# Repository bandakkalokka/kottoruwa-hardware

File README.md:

<!--
*** Thanks for checking out this README Template. If you have a suggestion that would
*** make this better, please fork the repo and create a pull request or simply open
*** an issue with the tag "enhancement".
*** Thanks again! Now go create something AMAZING! :D
-->

<!-- PROJECT SHIELDS -->
<!--
*** I'm using markdown "reference style" links for readability.
*** Reference links are enclosed in brackets [ ] instead of parentheses ( ).
*** See the bottom of this document for the declaration of the reference variables
*** for contributors-url, forks-url, etc. This is an optional, concise syntax you may use.
*** https://www.markdownguide.org/basic-syntax/#reference-style-links
-->
[![Contributors][contributors-shield]][contributors-url]
[![Forks][forks-shield]][forks-url]
[![Stargazers][stars-shield]][stars-url]
[![Issues][issues-shield]][issues-url]
[![MIT License][license-shield]][license-url]
<!-- [![LinkedIn][linkedin-shield]][linkedin-url] -->

<!-- PROJECT LOGO -->
<br />
<p align="center">

  <h3 align="center">Kottoruwa</h3>

  <p align="center">
    An awesome wireless mechanical keyboard with Li-Ion Battery Managemet, 2.4GHz radio and an OLED Display!
    <br />
    <a href="https://github.com/bandakkalokka/kottoruwa-hardware"><strong>Explore the docs »</strong></a>
    <br />
    <br />
    <!-- <a href="https://github.com/othneildrew/Best-README-Template">View Demo</a> 
    · -->
    <a href="https://github.com/bandakkalokka/kottoruwa-hardware/issues">Report Bug</a>
    ·
    <a href="https://github.com/bandakkalokka/kottoruwa-hardware/issues">Request Feature</a>
  </p>
</p>

<!-- TABLE OF CONTENTS -->
## Table of Contents

* [About the Project](#about-the-project)
  * [Built With](#built-with)
* [Project Structure](#project-structure)
* [Prerequisites](#prerequisites)
* [Roadmap](#roadmap)
* [Contributing](#contributing)
* [License](#license)
* [Contact](#contact)
* [Acknowledgements](#acknowledgements)

[![Product Name Screen Shot][product-screenshot]](https://example.com)

### Built With
* [KiCAD](https://docs.kicad-pcb.org/5.0/en/kicad/kicad.html)
* [QMK](https://qmk.fm/)

<!-- GETTING STARTED -->
## Project Structure

* 3d_models - .STEP and .WRL model files for all footprints
* datasheets - data sheets for components used
* gerbers - final production files
* images - SVG images and 3D board renders
* keeb-design-files - .pro, .sch and other KiCAD files
* lib_fp.pretty - footprints
* lib_sch - schematic symbols
* pdf - schematics, board layouts, dimension drawings

### Prerequisites

* KICAD (EESchema, PcbNew)
* PDF Viewer
* 3D Model Viewer

<!-- ROADMAP -->
## Roadmap

See the [open issues](https://github.com/bandakkalokka/kottoruwa-hardware/issues) for a list of proposed features (and known issues).

<!-- CONTRIBUTING -->
## Contributing

Contributions are what make the open source community such an amazing place to be learn, inspire, and create. Any contributions you make are **greatly appreciated**.

1. Fork the Project
2. Create your Feature Branch (`git checkout -b feature/AmazingFeature`)
3. Commit your Changes (`git commit -m 'Add some AmazingFeature'`)
4. Push to the Branch (`git push origin feature/AmazingFeature`)
5. Open a Pull Request

<!-- LICENSE -->
## License

Distributed under the GPL-3.0 License. See `LICENSE` for more information.

<!-- CONTACT -->
## Contact

rb28z2 - [@rb28z2](https://github.com/rb28z2) 
<br />
bandakkalokka - [@bandakkalokka](https://github.com/bandakkalokka)
<br />
Project Link: [https://github.com/bandakkalokka/kottoruwa-hardware](https://github.com/bandakkalokka/kottoruwa-hardware)

<!-- ACKNOWLEDGEMENTS -->
## 

* [QMK](https://github.com/qmk/qmk_firmware)

<!-- MARKDOWN LINKS & IMAGES -->
<!-- https://www.markdownguide.org/basic-syntax/#reference-style-links -->
[contributors-shield]: https://img.shields.io/github/contributors/bandakkalokka/kottoruwa-hardware.svg?style=flat-square
[contributors-url]: https://github.com/bandakkalokka/kottoruwa-hardware/graphs/contributors
[forks-shield]: https://img.shields.io/github/forks/bandakkalokka/kottoruwa-hardware.svg?style=flat-square
[forks-url]: https://github.com/bandakkalokka/kottoruwa-hardware/network/members
[stars-shield]: https://img.shields.io/github/stars/bandakkalokka/kottoruwa-hardware.svg?style=flat-square
[stars-url]: https://github.com/bandakkalokka/kottoruwa-hardware/stargazers
[issues-shield]: https://img.shields.io/github/issues/bandakkalokka/kottoruwa-hardware.svg?style=flat-square
[issues-url]: https://github.com/bandakkalokka/kottoruwa-hardware/issues
[license-shield]: https://img.shields.io/github/license/bandakkalokka/kottoruwa-hardware.svg?style=flat-square
[license-url]: https://github.com/bandakkalokka/kottoruwa-hardware/blob/master/LICENSE.txt
[linkedin-shield]: https://img.shields.io/badge/-LinkedIn-black.svg?style=flat-square&logo=linkedin&colorB=555
[linkedin-url]: https://linkedin.com/in/chathula-adikary-908450168/
[product-screenshot]: images/keeb-img.jpg

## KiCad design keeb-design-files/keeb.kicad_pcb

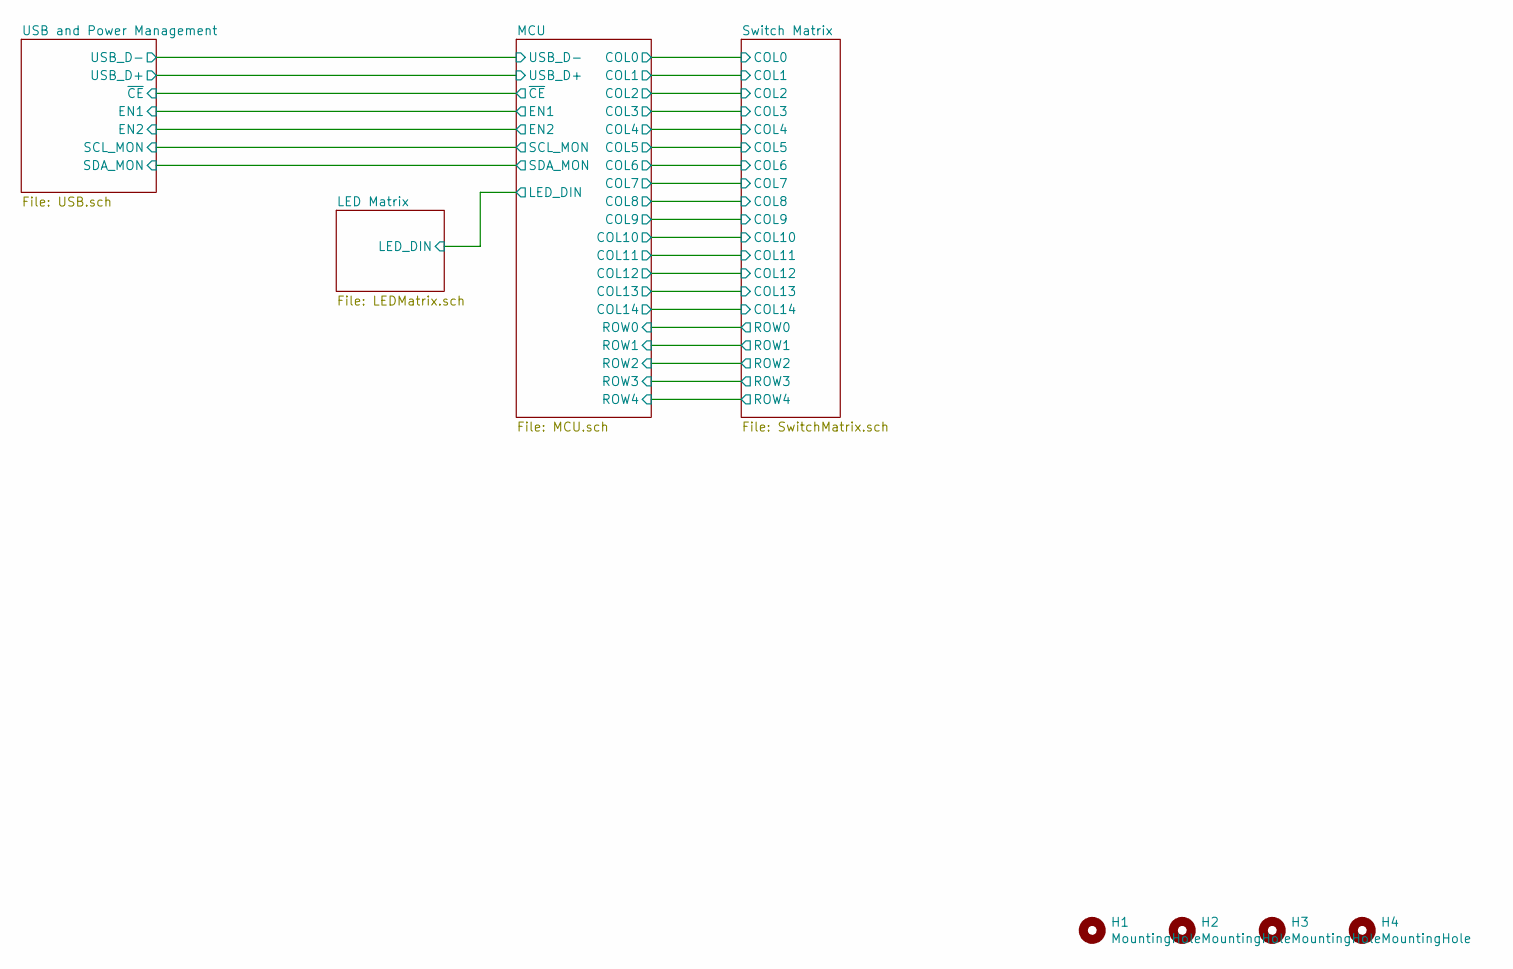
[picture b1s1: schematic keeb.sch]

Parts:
H1, H2, H3, H4: MountingHole; MountingHole_4.3mm_M4

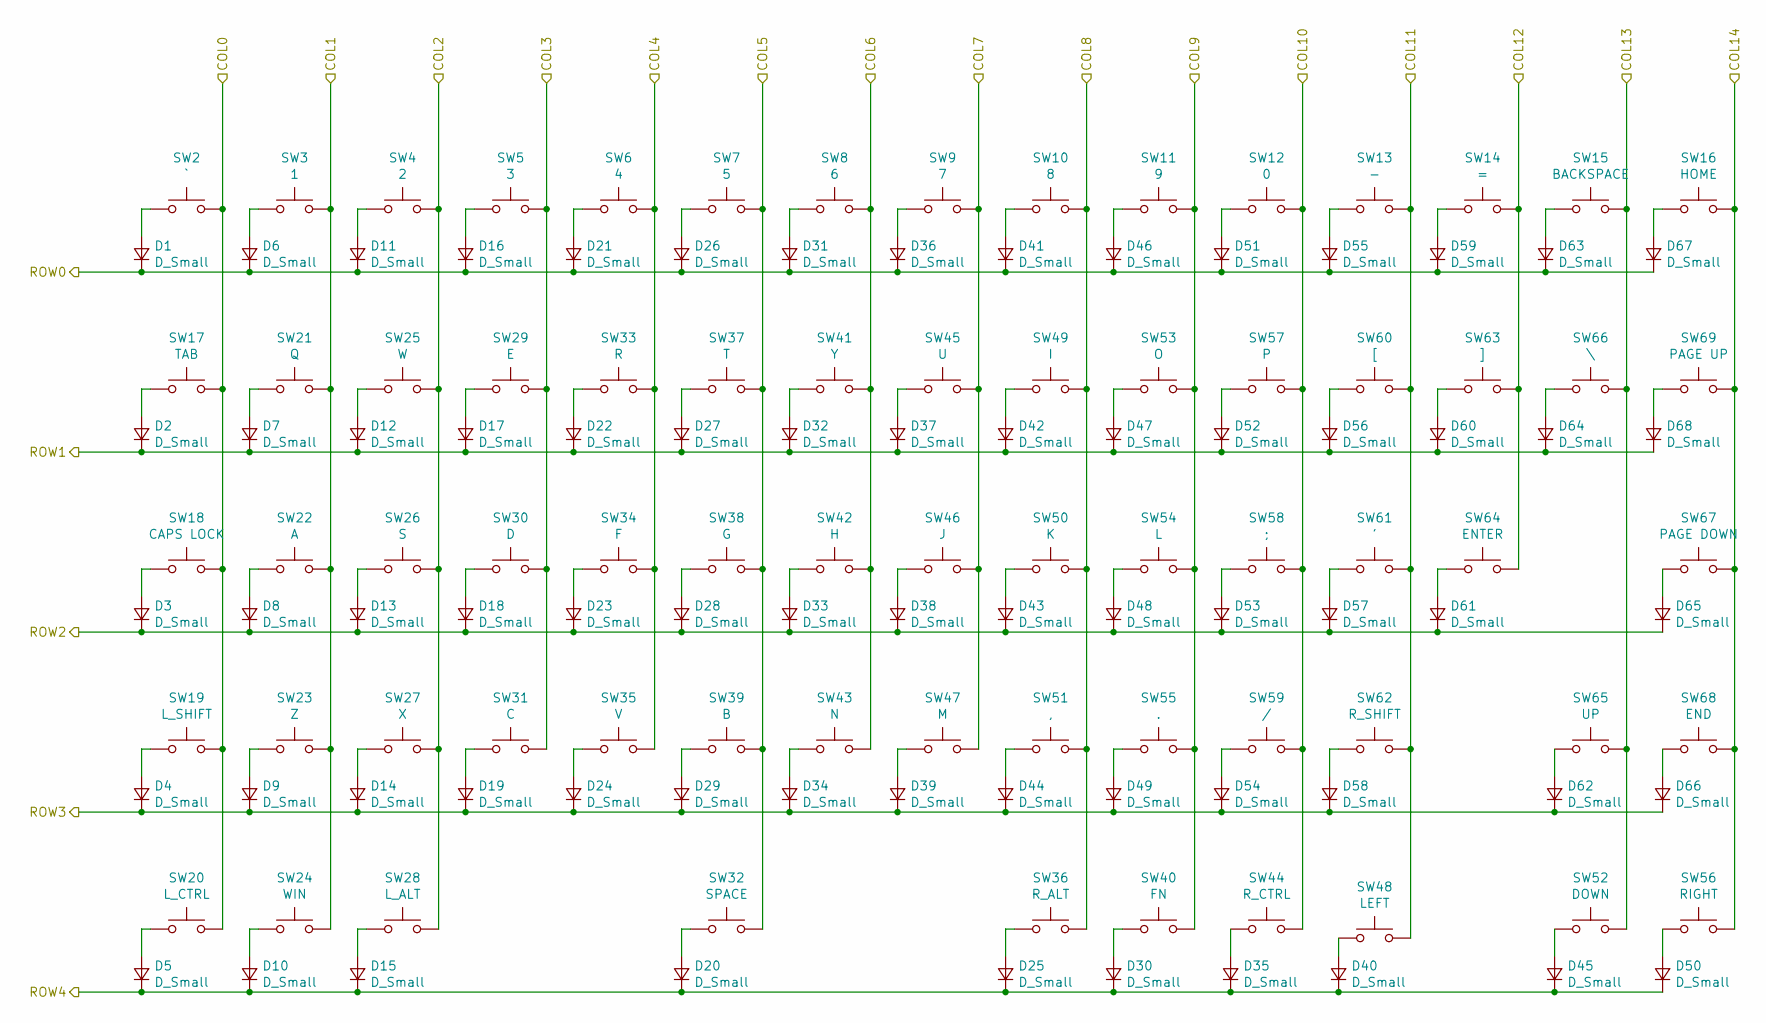
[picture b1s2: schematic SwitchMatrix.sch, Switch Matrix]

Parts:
D1, D2, D3, D4, D5, D6, D7, D8, D9, D10, D11, D12, D13, D14, D15, D16, D17, D18, D19, D20, D21, D22, D23, D24, D25, D26, D27, D28, D29, D30, D31, D32, D33, D34, D35, D36, D37, D38, D39, D40, D41, D42, D43, D44, D45, D46, D47, D48, D49, D50, D51, D52, D53, D54, D55, D56, D57, D58, D59, D60, D61, D62, D63, D64, D65, D66, D67, D68: D_Small; D_SOD-323_HandSoldering; LCSC Part Number C2128
SW2: `; MXOnly-1U-Hotswap
SW3: 1; MXOnly-1U-Hotswap
SW4: 2; MXOnly-1U-Hotswap
SW5: 3; MXOnly-1U-Hotswap
SW6: 4; MXOnly-1U-Hotswap
SW7: 5; MXOnly-1U-Hotswap
SW8: 6; MXOnly-1U-Hotswap
SW9: 7; MXOnly-1U-Hotswap
SW10: 8; MXOnly-1U-Hotswap
SW11: 9; MXOnly-1U-Hotswap
SW12: 0; MXOnly-1U-Hotswap
SW13: -; MXOnly-1U-Hotswap
SW14: =; MXOnly-1U-Hotswap
SW15: BACKSPACE; MXOnly-2U-Hotswap
SW16: HOME; MXOnly-1U-Hotswap
SW17: TAB; MXOnly-1.5U-Hotswap
SW18: CAPS LOCK; MXOnly-1.75U-Hotswap
SW19: L_SHIFT; MXOnly-2.25U-Hotswap
SW20: L_CTRL; MXOnly-1.25U-Hotswap
SW21: Q; MXOnly-1U-Hotswap
SW22: A; MXOnly-1U-Hotswap
SW23: Z; MXOnly-1U-Hotswap
SW24: WIN; MXOnly-1.25U-Hotswap
SW25: W; MXOnly-1U-Hotswap
SW26: S; MXOnly-1U-Hotswap
SW27: X; MXOnly-1U-Hotswap
SW28: L_ALT; MXOnly-1.25U-Hotswap
SW29: E; MXOnly-1U-Hotswap
SW30: D; MXOnly-1U-Hotswap
SW31: C; MXOnly-1U-Hotswap
SW32: SPACE; MXOnly-6.25U-Hotswap
SW33: R; MXOnly-1U-Hotswap
SW34: F; MXOnly-1U-Hotswap
SW35: V; MXOnly-1U-Hotswap
SW36: R_ALT; MXOnly-1U-Hotswap
SW37: T; MXOnly-1U-Hotswap
SW38: G; MXOnly-1U-Hotswap
SW39: B; MXOnly-1U-Hotswap
SW40: FN; MXOnly-1U-Hotswap
SW41: Y; MXOnly-1U-Hotswap
SW42: H; MXOnly-1U-Hotswap
SW43: N; MXOnly-1U-Hotswap
SW44: R_CTRL; MXOnly-1U-Hotswap
SW45: U; MXOnly-1U-Hotswap
SW46: J; MXOnly-1U-Hotswap
SW47: M; MXOnly-1U-Hotswap
SW48: LEFT; MXOnly-1U-Hotswap
SW49: I; MXOnly-1U-Hotswap
SW50: K; MXOnly-1U-Hotswap
SW51: ,; MXOnly-1U-Hotswap
SW52: DOWN; MXOnly-1U-Hotswap
SW53: O; MXOnly-1U-Hotswap
SW54: L; MXOnly-1U-Hotswap
SW55: .; MXOnly-1U-Hotswap
SW56: RIGHT; MXOnly-1U-Hotswap
SW57: P; MXOnly-1U-Hotswap
SW58: ;; MXOnly-1U-Hotswap
SW59: /; MXOnly-1U-Hotswap
SW60: [; MXOnly-1U-Hotswap
SW61: '; MXOnly-1U-Hotswap
SW62: R_SHIFT; MXOnly-1.75U-Hotswap
SW63: ]; MXOnly-1U-Hotswap
SW64: ENTER; MXOnly-2.25U-Hotswap
SW65: UP; MXOnly-1U-Hotswap
SW66: \\; MXOnly-1.5U-Hotswap
SW67: PAGE DOWN; MXOnly-1U-Hotswap
SW68: END; MXOnly-1U-Hotswap
SW69: PAGE UP; MXOnly-1U-Hotswap

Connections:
/MCU/COL0: SW2.2, SW17.2, SW18.2, SW19.2, SW20.2; also elsewhere on the board
/MCU/COL1: SW3.2, SW21.2, SW22.2, SW23.2, SW24.2; also elsewhere on the board
/MCU/COL2: SW4.2, SW25.2, SW26.2, SW27.2, SW28.2; also elsewhere on the board
/MCU/COL3: SW5.2, SW29.2, SW30.2, SW31.2; also elsewhere on the board
/MCU/COL4: SW6.2, SW33.2, SW34.2, SW35.2; also elsewhere on the board
/MCU/COL5: SW7.2, SW32.2, SW37.2, SW38.2, SW39.2; also elsewhere on the board
/MCU/COL6: SW8.2, SW41.2, SW42.2, SW43.2; also elsewhere on the board
/MCU/COL7: SW9.2, SW45.2, SW46.2, SW47.2; also elsewhere on the board
/MCU/COL8: SW10.2, SW36.2, SW49.2, SW50.2, SW51.2; also elsewhere on the board
/MCU/COL9: SW11.2, SW40.2, SW53.2, SW54.2, SW55.2; also elsewhere on the board
/MCU/COL10: SW12.2, SW44.2, SW57.2, SW58.2, SW59.2; also elsewhere on the board
/MCU/COL11: SW13.2, SW48.2, SW60.2, SW61.2, SW62.2; also elsewhere on the board
/MCU/COL12: SW14.2, SW63.2, SW64.2; also elsewhere on the board
/MCU/COL13: SW15.2, SW52.2, SW65.2, SW66.2; also elsewhere on the board
/MCU/COL14: SW16.2, SW56.2, SW67.2, SW68.2, SW69.2; also elsewhere on the board
/MCU/ROW0: D1.1 (K), D6.1 (K), D11.1 (K), D16.1 (K), D21.1 (K), D26.1 (K), D31.1 (K), D36.1 (K), D41.1 (K), D46.1 (K), D51.1 (K), D55.1 (K), D59.1 (K), D63.1 (K), D67.1 (K); also elsewhere on the board
/MCU/ROW1: D2.1 (K), D7.1 (K), D12.1 (K), D17.1 (K), D22.1 (K), D27.1 (K), D32.1 (K), D37.1 (K), D42.1 (K), D47.1 (K), D52.1 (K), D56.1 (K), D60.1 (K), D64.1 (K), D68.1 (K); also elsewhere on the board
/MCU/ROW2: D3.1 (K), D8.1 (K), D13.1 (K), D18.1 (K), D23.1 (K), D28.1 (K), D33.1 (K), D38.1 (K), D43.1 (K), D48.1 (K), D53.1 (K), D57.1 (K), D61.1 (K), D65.1 (K); also elsewhere on the board
/MCU/ROW3: D4.1 (K), D9.1 (K), D14.1 (K), D19.1 (K), D24.1 (K), D29.1 (K), D34.1 (K), D39.1 (K), D44.1 (K), D49.1 (K), D54.1 (K), D58.1 (K), D62.1 (K), D66.1 (K); also elsewhere on the board
/MCU/ROW4: D5.1 (K), D10.1 (K), D15.1 (K), D20.1 (K), D25.1 (K), D30.1 (K), D35.1 (K), D40.1 (K), D45.1 (K), D50.1 (K); also elsewhere on the board
unnamed: D1.2 (A), SW2.1
unnamed: D2.2 (A), SW17.1
unnamed: D3.2 (A), SW18.1
unnamed: D4.2 (A), SW19.1
unnamed: D5.2 (A), SW20.1
unnamed: D6.2 (A), SW3.1
unnamed: D7.2 (A), SW21.1
unnamed: D8.2 (A), SW22.1
unnamed: D9.2 (A), SW23.1
unnamed: D10.2 (A), SW24.1
unnamed: D11.2 (A), SW4.1
unnamed: D12.2 (A), SW25.1
unnamed: D13.2 (A), SW26.1
unnamed: D14.2 (A), SW27.1
unnamed: D15.2 (A), SW28.1
unnamed: D16.2 (A), SW5.1
unnamed: D17.2 (A), SW29.1
unnamed: D18.2 (A), SW30.1
unnamed: D19.2 (A), SW31.1
unnamed: D20.2 (A), SW32.1
unnamed: D21.2 (A), SW6.1
unnamed: D22.2 (A), SW33.1
unnamed: D23.2 (A), SW34.1
unnamed: D24.2 (A), SW35.1
unnamed: D25.2 (A), SW36.1
unnamed: D26.2 (A), SW7.1
unnamed: D27.2 (A), SW37.1
unnamed: D28.2 (A), SW38.1
unnamed: D29.2 (A), SW39.1
unnamed: D30.2 (A), SW40.1
unnamed: D31.2 (A), SW8.1
unnamed: D32.2 (A), SW41.1
unnamed: D33.2 (A), SW42.1
unnamed: D34.2 (A), SW43.1
unnamed: D35.2 (A), SW44.1
unnamed: D36.2 (A), SW9.1
unnamed: D37.2 (A), SW45.1
unnamed: D38.2 (A), SW46.1
unnamed: D39.2 (A), SW47.1
unnamed: D40.2 (A), SW48.1
unnamed: D41.2 (A), SW10.1
unnamed: D42.2 (A), SW49.1
unnamed: D43.2 (A), SW50.1
unnamed: D44.2 (A), SW51.1
unnamed: D45.2 (A), SW52.1
unnamed: D46.2 (A), SW11.1
unnamed: D47.2 (A), SW53.1
unnamed: D48.2 (A), SW54.1
unnamed: D49.2 (A), SW55.1
unnamed: D50.2 (A), SW56.1
unnamed: D51.2 (A), SW12.1
unnamed: D52.2 (A), SW57.1
unnamed: D53.2 (A), SW58.1
unnamed: D54.2 (A), SW59.1
unnamed: D55.2 (A), SW13.1
unnamed: D56.2 (A), SW60.1
unnamed: D57.2 (A), SW61.1
unnamed: D58.2 (A), SW62.1
unnamed: D59.2 (A), SW14.1
unnamed: D60.2 (A), SW63.1
unnamed: D61.2 (A), SW64.1
unnamed: D62.2 (A), SW65.1
unnamed: D63.2 (A), SW15.1
unnamed: D64.2 (A), SW66.1
unnamed: D65.2 (A), SW67.1
unnamed: D66.2 (A), SW68.1
unnamed: D67.2 (A), SW16.1
unnamed: D68.2 (A), SW69.1

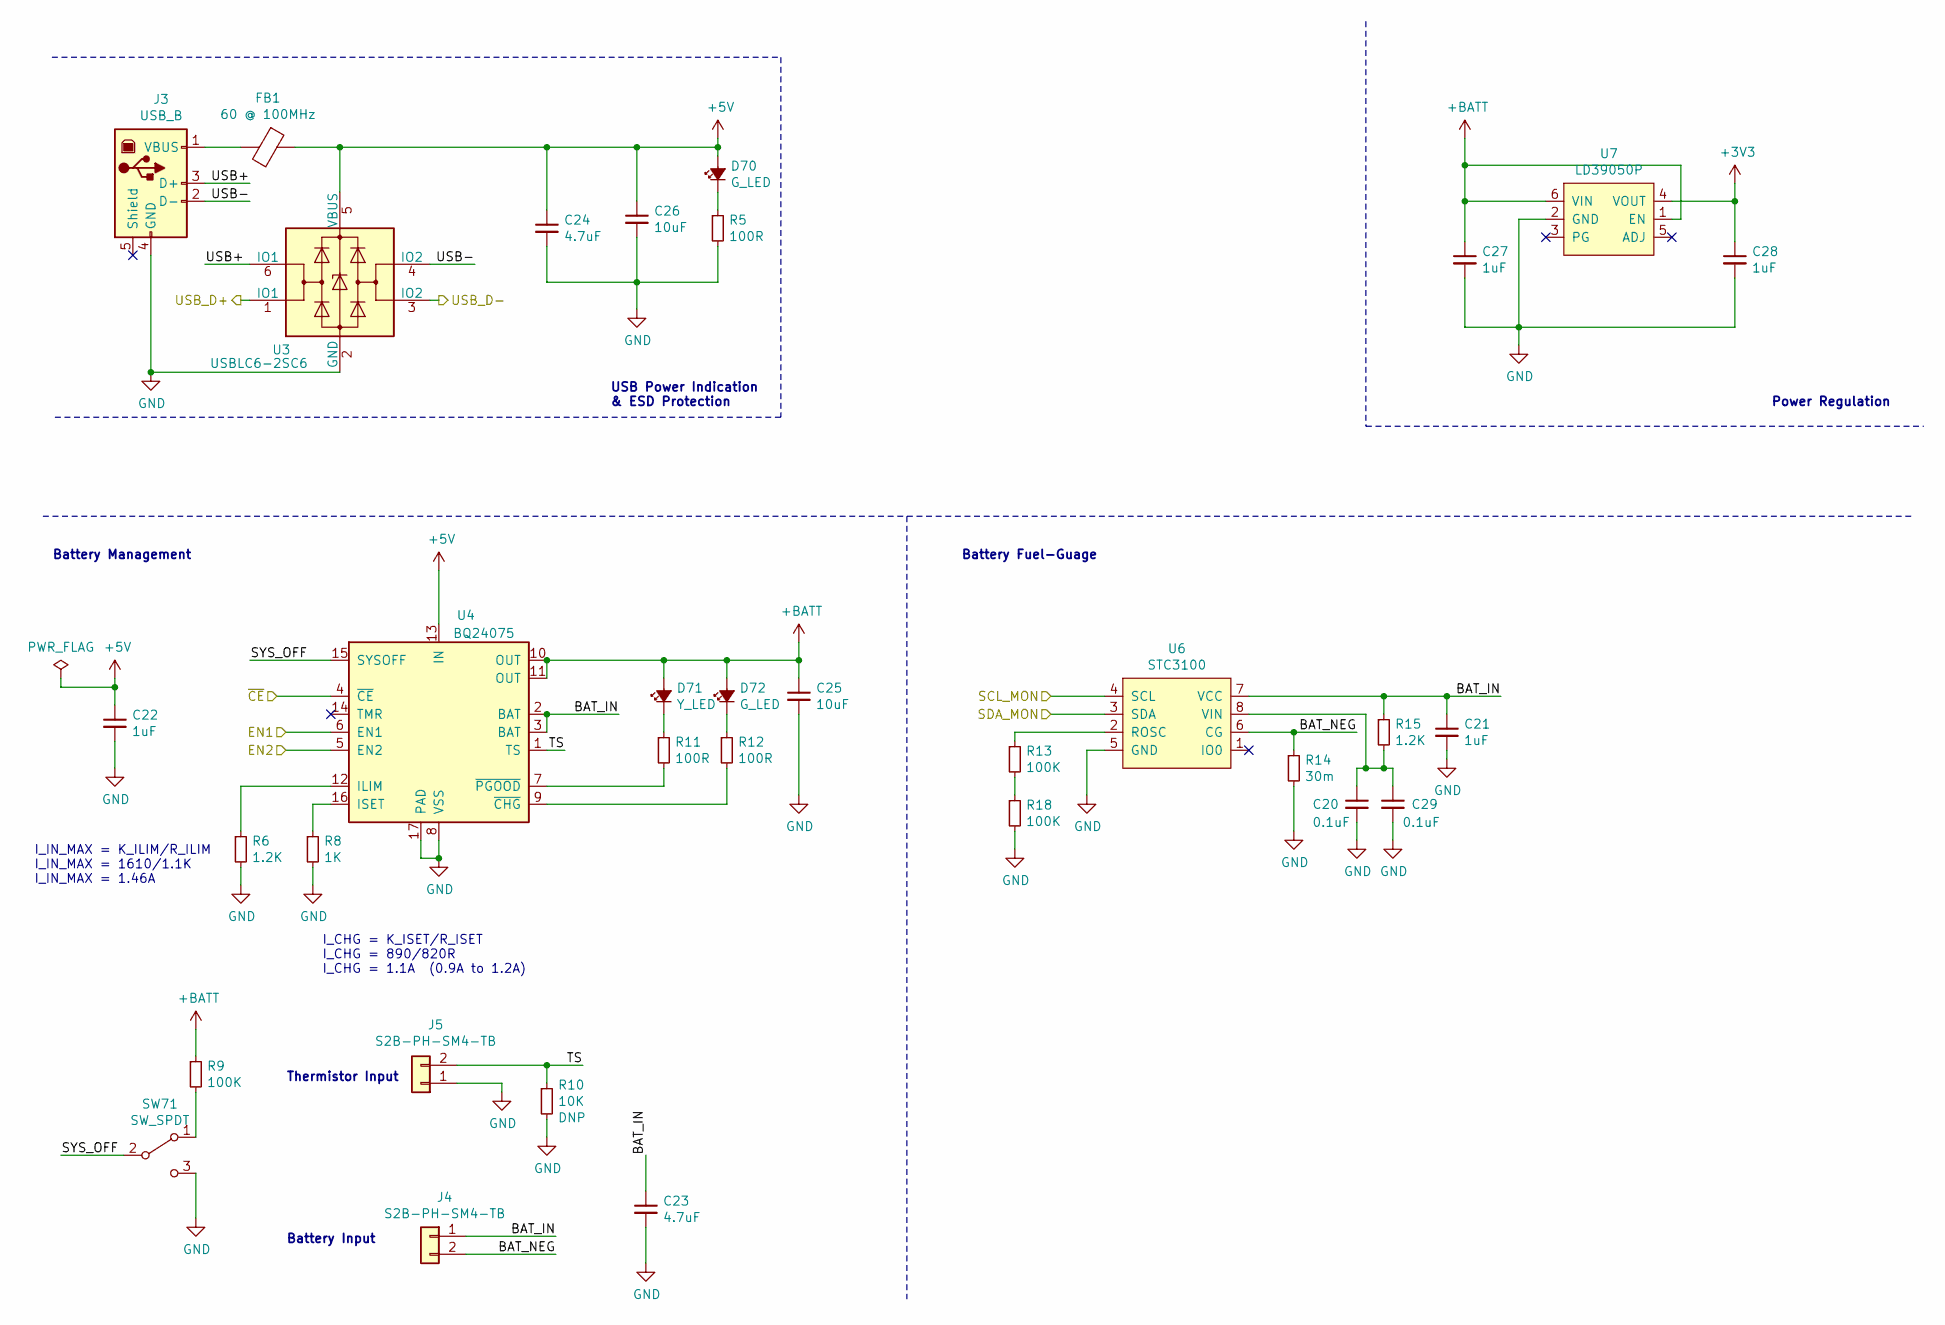
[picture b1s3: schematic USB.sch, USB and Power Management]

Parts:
C20, C29: 0.1uF; C_0402_1005Metric; LCSC Part Number C1525
C21, C22, C27, C28: 1uF; C_0402_1005Metric; LCSC Part Number C52923
C23, C24: 4.7uF; C_0603_1608Metric; LCSC Part Number C19666
C25, C26: 10uF; C_0603_1608Metric; LCSC Part Number C19702
D70, D72: G_LED; LED_0603_1608Metric; LCSC Part Number C72043
D71: Y_LED; LED_0603_1608Metric; LCSC Part Number C72038
FB1: 60 @ 100MHz; R_0603_1608Metric_Pad1.05x0.95mm_HandSolder; LCSC Part Number C76816
J3: USB_B; USB-B1HSW6
J4, J5: S2B-PH-SM4-TB; JST_PH_S2B-PH-SM4-TB_1x02-1MP_P2.00mm_Horizontal
R5, R11, R12: 100R; R_0402_1005Metric; LCSC Part Number C25076
R6, R15: 1.2K; R_0402_1005Metric; LCSC Part Number C25862
R8: 1K; R_0402_1005Metric; LCSC Part Number C11702
R9, R13, R18: 100K; R_0402_1005Metric; LCSC Part Number C25741
R10: 10K; R_0603_1608Metric_Pad1.05x0.95mm_HandSolder; LCSC Part Number DNP
R14: 30m; R_0805_2012Metric; LCSC Part Number C247605
SW71: SW_SPDT; SW_CuK_OS102011MA1QN1_SPDT_Angled
U3: USBLC6-2SC6; SOT-23-6; LCSC Part Number C7519
U4: BQ24075; QFN-16-1EP_3x3mm_P0.5mm_EP1.7x1.7mm; LCSC Part Number C15464
U6: STC3100; DFN-8-1EP_3x3mm_P0.5mm_EP1.66x2.38mm; LCSC Part Number C155587
U7: LD39050P; DFN-6-1EP_3x3mm_P0.95mm_EP1.7x2.6mm; LCSC Part Number C132827

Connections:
+3V3: C28.1, U7.4 (VOUT); also elsewhere on the board
+5V: C22.1, C24.1, C26.1, D70.2 (A), FB1.1, U3.5 (VBUS), U4.13 (IN)
+BATT: C25.1, C27.1, D71.2 (A), D72.2 (A), R9.1, U4.10 (OUT), U4.11 (OUT), U7.1 (EN), U7.6 (VIN)
/MCU/EN1: U4.6 (EN1); also elsewhere on the board
/MCU/EN2: U4.5 (EN2); also elsewhere on the board
/MCU/SCL_MON: U6.4 (SCL); also elsewhere on the board
/MCU/SDA_MON: U6.3 (SDA); also elsewhere on the board
/MCU/USB_D+: U3.1 (IO1); also elsewhere on the board
/MCU/USB_D-: U3.3 (IO2); also elsewhere on the board
/MCU/~CE~: U4.4 (~CE); also elsewhere on the board
/USB and Power Management/BAT_IN: C21.1, C23.1, J4.1, R15.1, U4.2 (BAT), U4.3 (BAT), U6.7 (VCC)
/USB and Power Management/BAT_NEG: J4.2, R14.1, U6.6 (CG)
/USB and Power Management/SYS_OFF: SW71.2 (B), U4.15 (SYSOFF)
/USB and Power Management/TS: J5.2, R10.1, U4.1 (TS)
/USB and Power Management/USB+: J3.3 (D+), U3.6 (IO1)
/USB and Power Management/USB-: J3.2 (D-), U3.4 (IO2)
GND: C20.2, C21.2, C22.2, C23.2, C24.2, C25.2, C26.2, C27.2, C28.2, C29.2, J3.4 (GND), J5.1, R5.2, R6.2, R8.2, R10.2, R14.2, R18.2, SW71.3 (C), U3.2 (GND), U4.8 (VSS), U4.17 (PAD), U6.5 (GND), U6.9, U7.2 (GND), U7.7; also elsewhere on the board
unnamed: C20.1, C29.1, R15.2, U6.8 (VIN)
unnamed: D70.1 (K), R5.1
unnamed: D71.1 (K), R11.1
unnamed: D72.1 (K), R12.1
unnamed: FB1.2, J3.1 (VBUS)
unnamed: R6.1, U4.12 (ILIM)
unnamed: R8.1, U4.16 (ISET)
unnamed: R9.2, SW71.1 (A)
unnamed: R11.2, U4.7 (~PGOOD)
unnamed: R12.2, U4.9 (~CHG)
unnamed: R13.1, U6.2 (ROSC)
unnamed: R13.2, R18.1

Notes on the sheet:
USB Power Indication & ESD Protection
I_CHG = K_ISET/R_ISET I_CHG = 890/820R I_CHG = 1.1A (0.9A to 1.2A)
I_IN_MAX = K_ILIM/R_ILIM I_IN_MAX = 1610/1.1K I_IN_MAX = 1.46A
Power Regulation
Thermistor Input
Battery Input
Battery Management
Battery Fuel-Guage

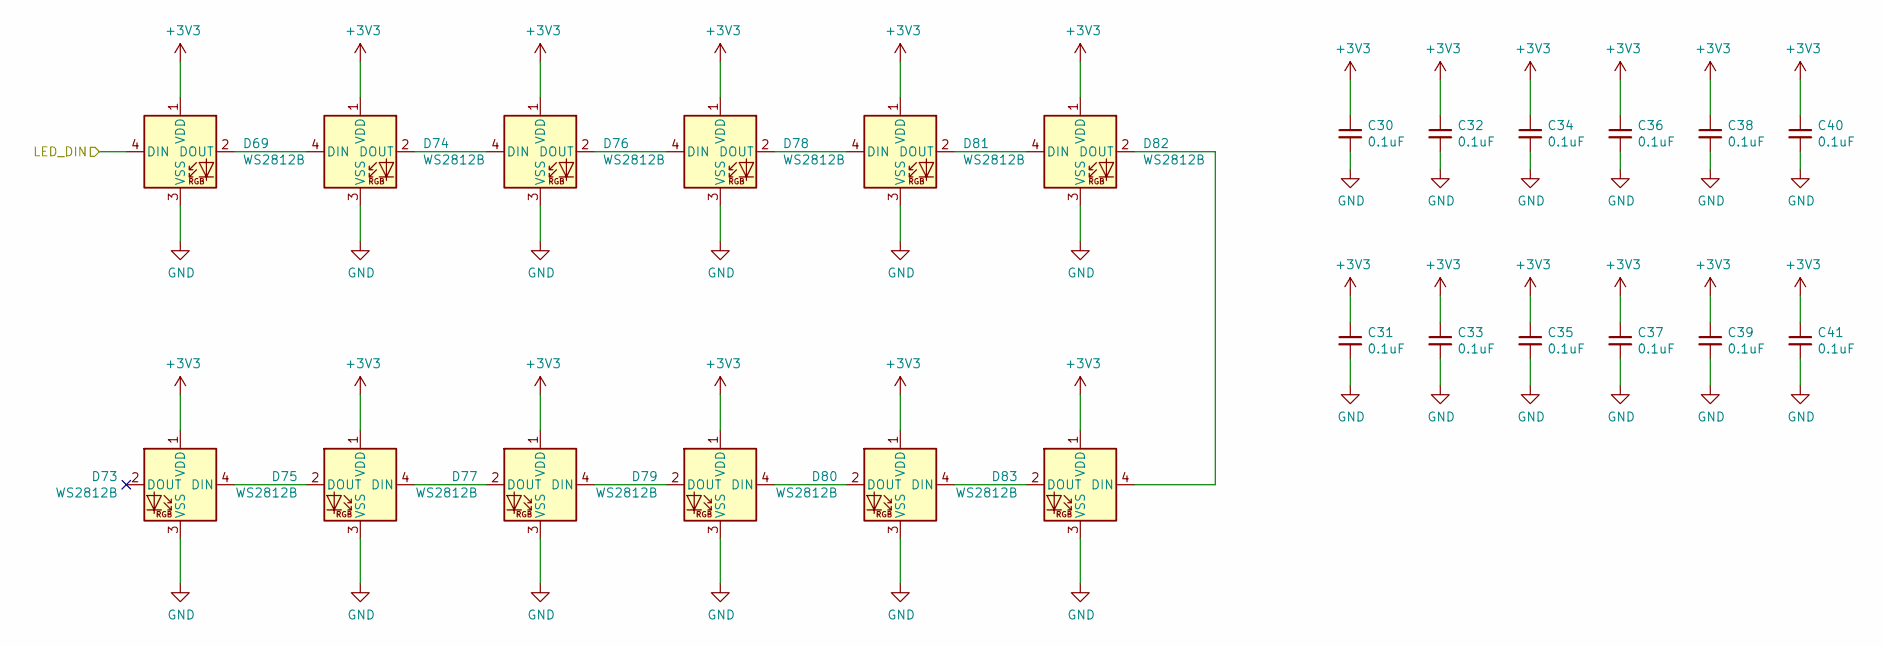
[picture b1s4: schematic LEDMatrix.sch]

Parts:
C30, C31, C32, C33, C34, C35, C36, C37, C38, C39, C40, C41: 0.1uF; C_0402_1005Metric; LCSC Part Number C1525
D69, D73, D74, D75, D76, D77, D78, D79, D80, D81, D82, D83: WS2812B; LED_WS2812B_PLCC4_5.0x5.0mm_P3.2mm; LCSC Part Number C114586

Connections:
+3V3: C30.1, C31.1, C32.1, C33.1, C34.1, C35.1, C36.1, C37.1, C38.1, C39.1, C40.1, C41.1, D69.1 (VDD), D73.1 (VDD), D74.1 (VDD), D75.1 (VDD), D76.1 (VDD), D77.1 (VDD), D78.1 (VDD), D79.1 (VDD), D80.1 (VDD), D81.1 (VDD), D82.1 (VDD), D83.1 (VDD); also elsewhere on the board
/LED Matrix/LED_DIN: D69.4 (DIN); also elsewhere on the board
GND: C30.2, C31.2, C32.2, C33.2, C34.2, C35.2, C36.2, C37.2, C38.2, C39.2, C40.2, C41.2, D69.3 (VSS), D73.3 (VSS), D74.3 (VSS), D75.3 (VSS), D76.3 (VSS), D77.3 (VSS), D78.3 (VSS), D79.3 (VSS), D80.3 (VSS), D81.3 (VSS), D82.3 (VSS), D83.3 (VSS); also elsewhere on the board
unnamed: D69.2 (DOUT), D74.4 (DIN)
unnamed: D73.4 (DIN), D75.2 (DOUT)
unnamed: D74.2 (DOUT), D76.4 (DIN)
unnamed: D75.4 (DIN), D77.2 (DOUT)
unnamed: D76.2 (DOUT), D78.4 (DIN)
unnamed: D77.4 (DIN), D79.2 (DOUT)
unnamed: D78.2 (DOUT), D81.4 (DIN)
unnamed: D79.4 (DIN), D80.2 (DOUT)
unnamed: D80.4 (DIN), D83.2 (DOUT)
unnamed: D81.2 (DOUT), D82.4 (DIN)
unnamed: D82.2 (DOUT), D83.4 (DIN)

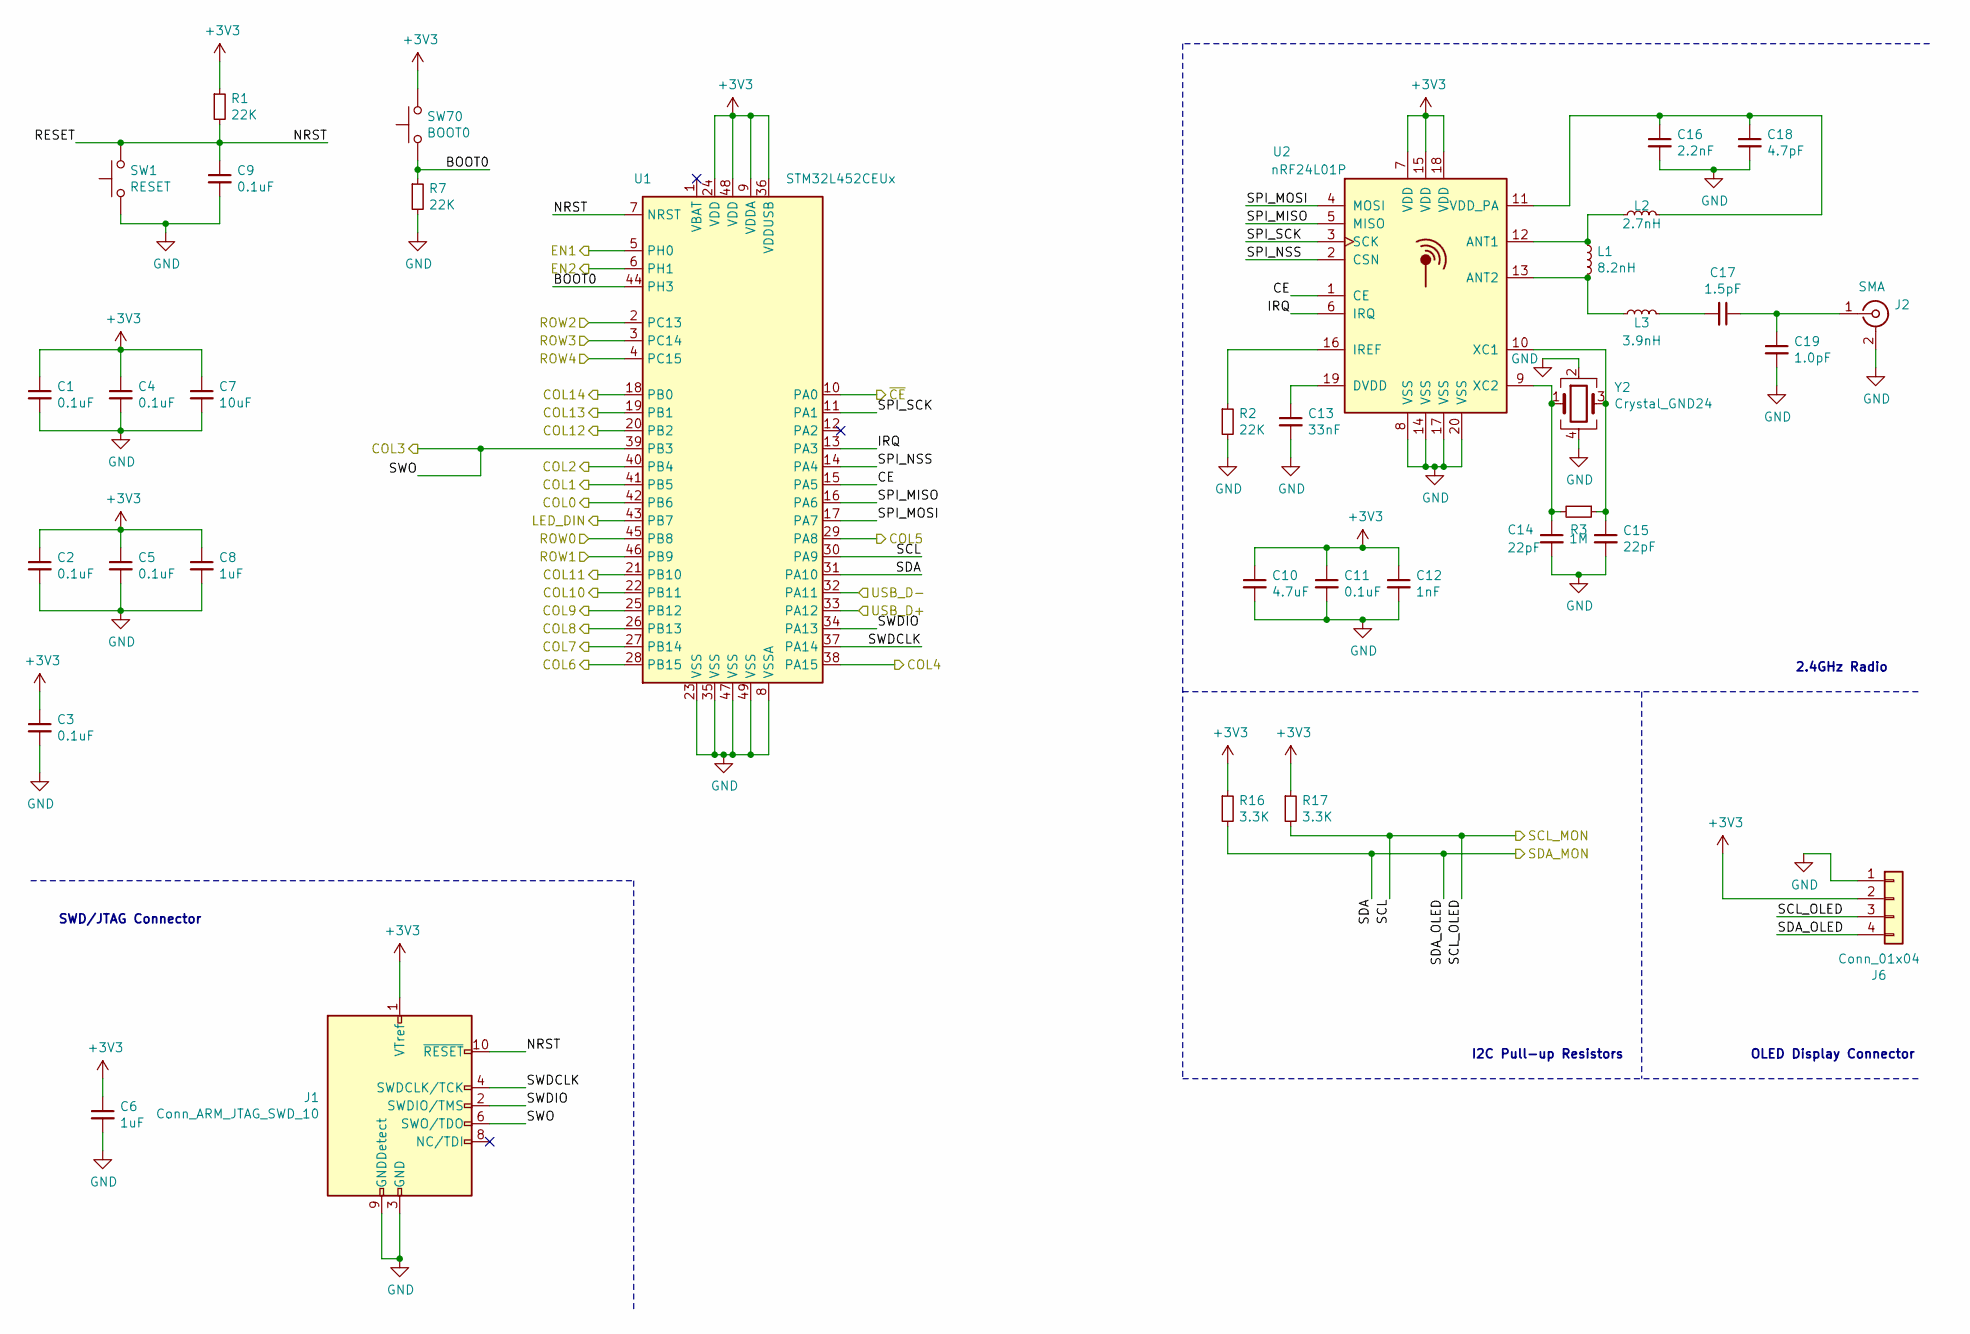
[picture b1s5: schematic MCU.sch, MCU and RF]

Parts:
C1, C2, C3, C4, C5, C9, C11: 0.1uF; C_0402_1005Metric; LCSC Part Number C1525
C6, C8: 1uF; C_0402_1005Metric; LCSC Part Number C52923
C7: 10uF; C_0603_1608Metric; LCSC Part Number C19702
C10: 4.7uF; C_0603_1608Metric; LCSC Part Number C19666
C12: 1nF; C_0402_1005Metric; LCSC Part Number C1523
C13: 33nF; C_0402_1005Metric; LCSC Part Number C1585
C14, C15: 22pF; C_0402_1005Metric; LCSC Part Number C1555
C16: 2.2nF; C_0402_1005Metric; LCSC Part Number C1531
C17: 1.5pF; C_0402_1005Metric; LCSC Part Number C1552
C18: 4.7pF; C_0402_1005Metric; LCSC Part Number C1569
C19: 1.0pF; C_0402_1005Metric; LCSC Part Number C1550
J1: Conn_ARM_JTAG_SWD_10; PinHeader_2x05_P1.27mm_Vertical_SMD
J2: SMA; SMA_Amphenol_132289_EdgeMount
J6: Conn_01x04; OLED_Display
L1: 8.2nH; L_0402_1005Metric; LCSC Part Number C16208
L2: 2.7nH; L_0402_1005Metric; LCSC Part Number C27123
L3: 3.9nH; L_0402_1005Metric; LCSC Part Number C13818
R1, R2, R7: 22K; R_0402_1005Metric; LCSC Part Number C25768
R3: 1M; R_0603_1608Metric_Pad1.05x0.95mm_HandSolder
R16, R17: 3.3K; R_0603_1608Metric_Pad1.05x0.95mm_HandSolder; LCSC Part Number C22978
SW1: RESET; SW_SPST_B3S-1000
SW70: BOOT0; SW_SPST_B3S-1000
U1: STM32L452CEUx; QFN-48-1EP_7x7mm_P0.5mm_EP5.6x5.6mm; LCSC Part Number C222355
U2: nRF24L01P; QFN-20-1EP_4x4mm_P0.5mm_EP2.5x2.5mm; LCSC Part Number C8791
Y2: Crystal_GND24; Crystal_SMD_3225-4Pin_3.2x2.5mm; LCSC Part Number C12668

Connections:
+3V3: C1.1, C2.1, C3.1, C4.1, C5.1, C6.1, C7.1, C8.1, C10.1, C11.1, C12.1, J1.1 (VTref), J6.2, R1.1, R16.1, R17.1, SW70.2, U1.9 (VDDA), U1.24 (VDD), U1.36 (VDDUSB), U1.48 (VDD), U2.7 (VDD), U2.15 (VDD), U2.18 (VDD); also elsewhere on the board
/LED Matrix/LED_DIN: U1.43 (PB7); also elsewhere on the board
/MCU/BOOT0: R7.1, SW70.1, U1.44 (PH3)
/MCU/CE: U1.15 (PA5), U2.1 (CE)
/MCU/COL0: U1.42 (PB6); also elsewhere on the board
/MCU/COL1: U1.41 (PB5); also elsewhere on the board
/MCU/COL2: U1.40 (PB4); also elsewhere on the board
/MCU/COL3: J1.6 (SWO/TDO), U1.39 (PB3); also elsewhere on the board
/MCU/COL4: U1.38 (PA15); also elsewhere on the board
/MCU/COL5: U1.29 (PA8); also elsewhere on the board
/MCU/COL6: U1.28 (PB15); also elsewhere on the board
/MCU/COL7: U1.27 (PB14); also elsewhere on the board
/MCU/COL8: U1.26 (PB13); also elsewhere on the board
/MCU/COL9: U1.25 (PB12); also elsewhere on the board
/MCU/COL10: U1.22 (PB11); also elsewhere on the board
/MCU/COL11: U1.21 (PB10); also elsewhere on the board
/MCU/COL12: U1.20 (PB2); also elsewhere on the board
/MCU/COL13: U1.19 (PB1); also elsewhere on the board
/MCU/COL14: U1.18 (PB0); also elsewhere on the board
/MCU/EN1: U1.5 (PH0); also elsewhere on the board
/MCU/EN2: U1.6 (PH1); also elsewhere on the board
/MCU/IRQ: U1.13 (PA3), U2.6 (IRQ)
/MCU/NRST: C9.1, J1.10 (~RESET~), R1.2, SW1.2, U1.7 (NRST)
/MCU/ROW0: U1.45 (PB8); also elsewhere on the board
/MCU/ROW1: U1.46 (PB9); also elsewhere on the board
/MCU/ROW2: U1.2 (PC13); also elsewhere on the board
/MCU/ROW3: U1.3 (PC14); also elsewhere on the board
/MCU/ROW4: U1.4 (PC15); also elsewhere on the board
/MCU/SCL_MON: J6.3, R17.2, U1.30 (PA9); also elsewhere on the board
/MCU/SDA_MON: J6.4, R16.2, U1.31 (PA10); also elsewhere on the board
/MCU/SPI_MISO: U1.16 (PA6), U2.5 (MISO)
/MCU/SPI_MOSI: U1.17 (PA7), U2.4 (MOSI)
/MCU/SPI_NSS: U1.14 (PA4), U2.2 (CSN)
/MCU/SPI_SCK: U1.11 (PA1), U2.3 (SCK)
/MCU/SWDCLK: J1.4 (SWDCLK/TCK), U1.37 (PA14)
/MCU/SWDIO: J1.2 (SWDIO/TMS), U1.34 (PA13)
/MCU/USB_D+: U1.33 (PA12); also elsewhere on the board
/MCU/USB_D-: U1.32 (PA11); also elsewhere on the board
/MCU/~CE~: U1.10 (PA0); also elsewhere on the board
GND: C1.2, C2.2, C3.2, C4.2, C5.2, C6.2, C7.2, C8.2, C9.2, C10.2, C11.2, C12.2, C13.2, C14.2, C15.2, C16.2, C18.2, C19.2, J1.3 (GND), J1.5 (GND), J1.9 (GNDDetect), J2.2 (Ext), J6.1, R2.2, R7.2, SW1.1, U1.8 (VSSA), U1.23 (VSS), U1.35 (VSS), U1.47 (VSS), U1.49 (VSS), U2.8 (VSS), U2.14 (VSS), U2.17 (VSS), U2.20 (VSS), U2.21, Y2.2, Y2.4; also elsewhere on the board
unnamed: C13.1, U2.19 (DVDD)
unnamed: C14.1, R3.2, U2.9 (XC2), Y2.1
unnamed: C15.1, R3.1, U2.10 (XC1), Y2.3
unnamed: C16.1, C18.1, L2.2, U2.11 (VDD_PA)
unnamed: C17.1, C19.1, J2.1 (In)
unnamed: C17.2, L3.2
unnamed: L1.1, L2.1, U2.12 (ANT1)
unnamed: L1.2, L3.1, U2.13 (ANT2)
unnamed: R2.1, U2.16 (IREF)

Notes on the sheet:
2.4GHz Radio
OLED Display Connector
SWD/JTAG Connector
I2C Pull-up Resistors

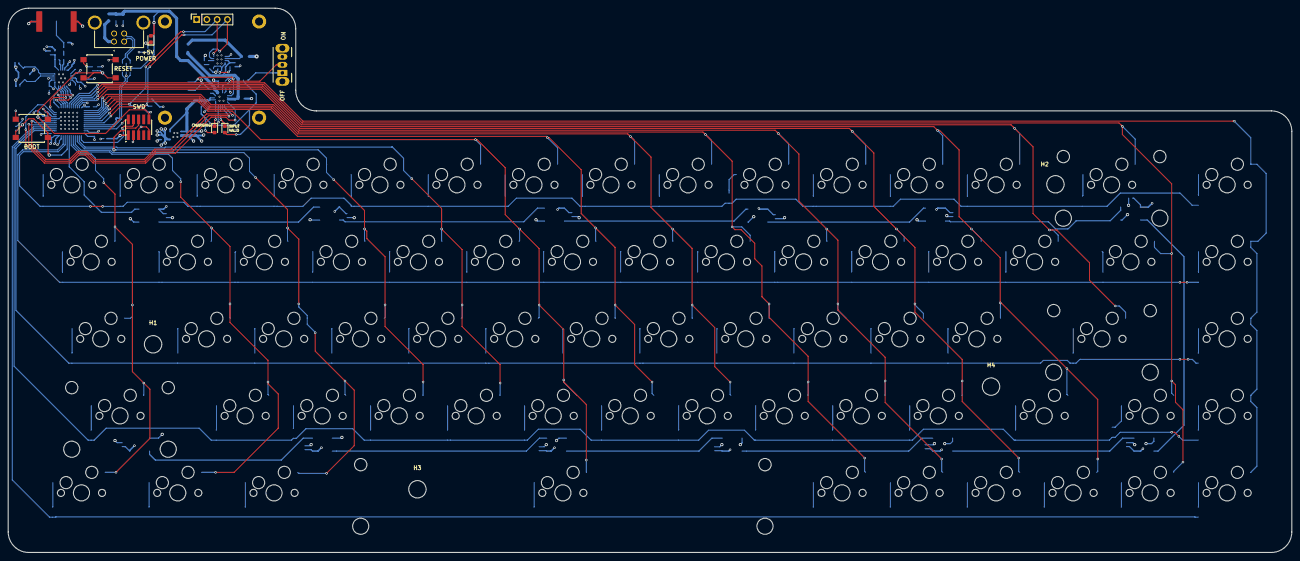
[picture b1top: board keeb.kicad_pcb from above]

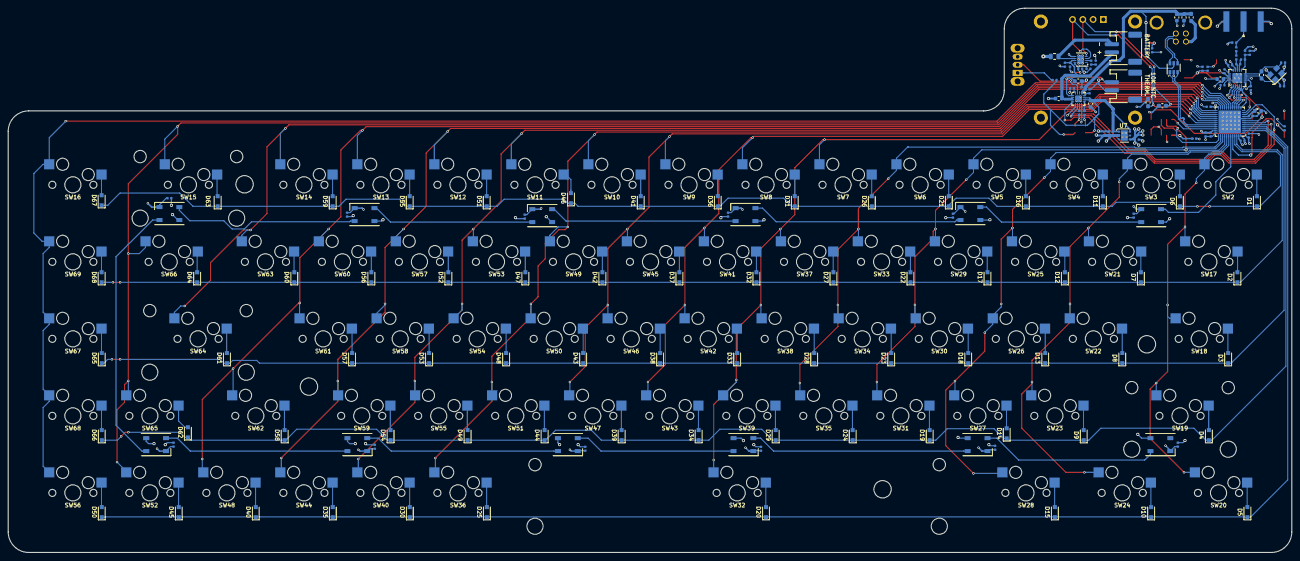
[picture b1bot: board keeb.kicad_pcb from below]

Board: 4 copper layers, 317.5 x 134.6 mm, 233 parts (152 on the bottom side), 148 nets.

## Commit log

2020-05-07 Remove unwanted footprints
2020-05-07 Remove Power Management Schematic
2020-05-08 Modify Key Switch path references to be relative rather than absolute in fp-lib-table
2020-05-08 Add new Crystal and match symbols and footprints for switches and diodes
2020-05-08 Remove back files
2020-05-08 Remove more bak files
2020-05-08 Modify .gitignore to include all bak files
2020-05-08 Add Reference Manual and create LD39050 symbol
2020-05-08 Add ESD diodes, USB isolator and LDO to schematic
2020-05-09 Start Battery Management and routed matrix to STM32L0
2020-05-14 Add more part #'s, change to STM32L452CEUxx MCU, more layout work
2020-05-16 Add 3D Model for Slide Switch
2020-05-16 Add Datasheet for BQ24075 Battery Monitor
2020-05-16 Add CAD drawing of OLED Display
2020-05-16 Create footprint for OLED Display and Slide Switch
2020-05-16 Add Battery Input, Thermistor Input, and SYSOFF Switch
2020-05-16 Add new connections to MCU for I2C OLED Display and Battery Management
2020-05-16 Connect USB Hierarchical pins to MCU
2020-05-18 Add 3D model for BQ24075 IC
2020-05-18 Create lib for STC3100 Fuel Guage
2020-05-18 Add I2C Pull-ups, Add STC3100 Fuel Guage
2020-05-18 Fix minor Batter Management issue
2020-05-20 Modify LD39050P to not be a Power Symbol
2020-05-20 Confirm LCSC part numbers, started placement for layout
2020-05-20 More placement before layout
2020-05-22 Add 3D Models for, OLED, Buttons, USB-B and SMT JSTConnector
2020-05-22 Add 3D Models to Footprints
2020-05-22 Re-map MCU pins, Add LEDs, Remove USB Isolation cause it couldn't handle the POWER! More routing done
2020-05-23 More routing added planes and re-wired MCU a bit
2020-05-25 Create gerbers picknplace and bom
2020-07-15 Add MCU datasheet and iamges for README
2020-07-15 Modify README
2020-07-15 Re-Generate Gerbers
2020-07-15 Modify the README some more
2020-07-20 fix README
